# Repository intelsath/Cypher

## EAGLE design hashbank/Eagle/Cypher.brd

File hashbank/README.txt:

For database (SQLITE) use:
move sqlite3 to /usr/local/bin

For nodejs use:
move nodejs to /usr/bin

bin files in hashbank/bin

Update nodejs to latest version:
curl -sL https://deb.nodesource.com/setup_8.x | sudo -E bash -
sudo apt-get install -y nodejs

NFC
Follow the instructions at: https://www.nxp.com/docs/en/application-note/AN11697.pdf

move /NFC/conf/ files to /usr/local/etc
move /NFC/libs/ files to /usr/local/lib

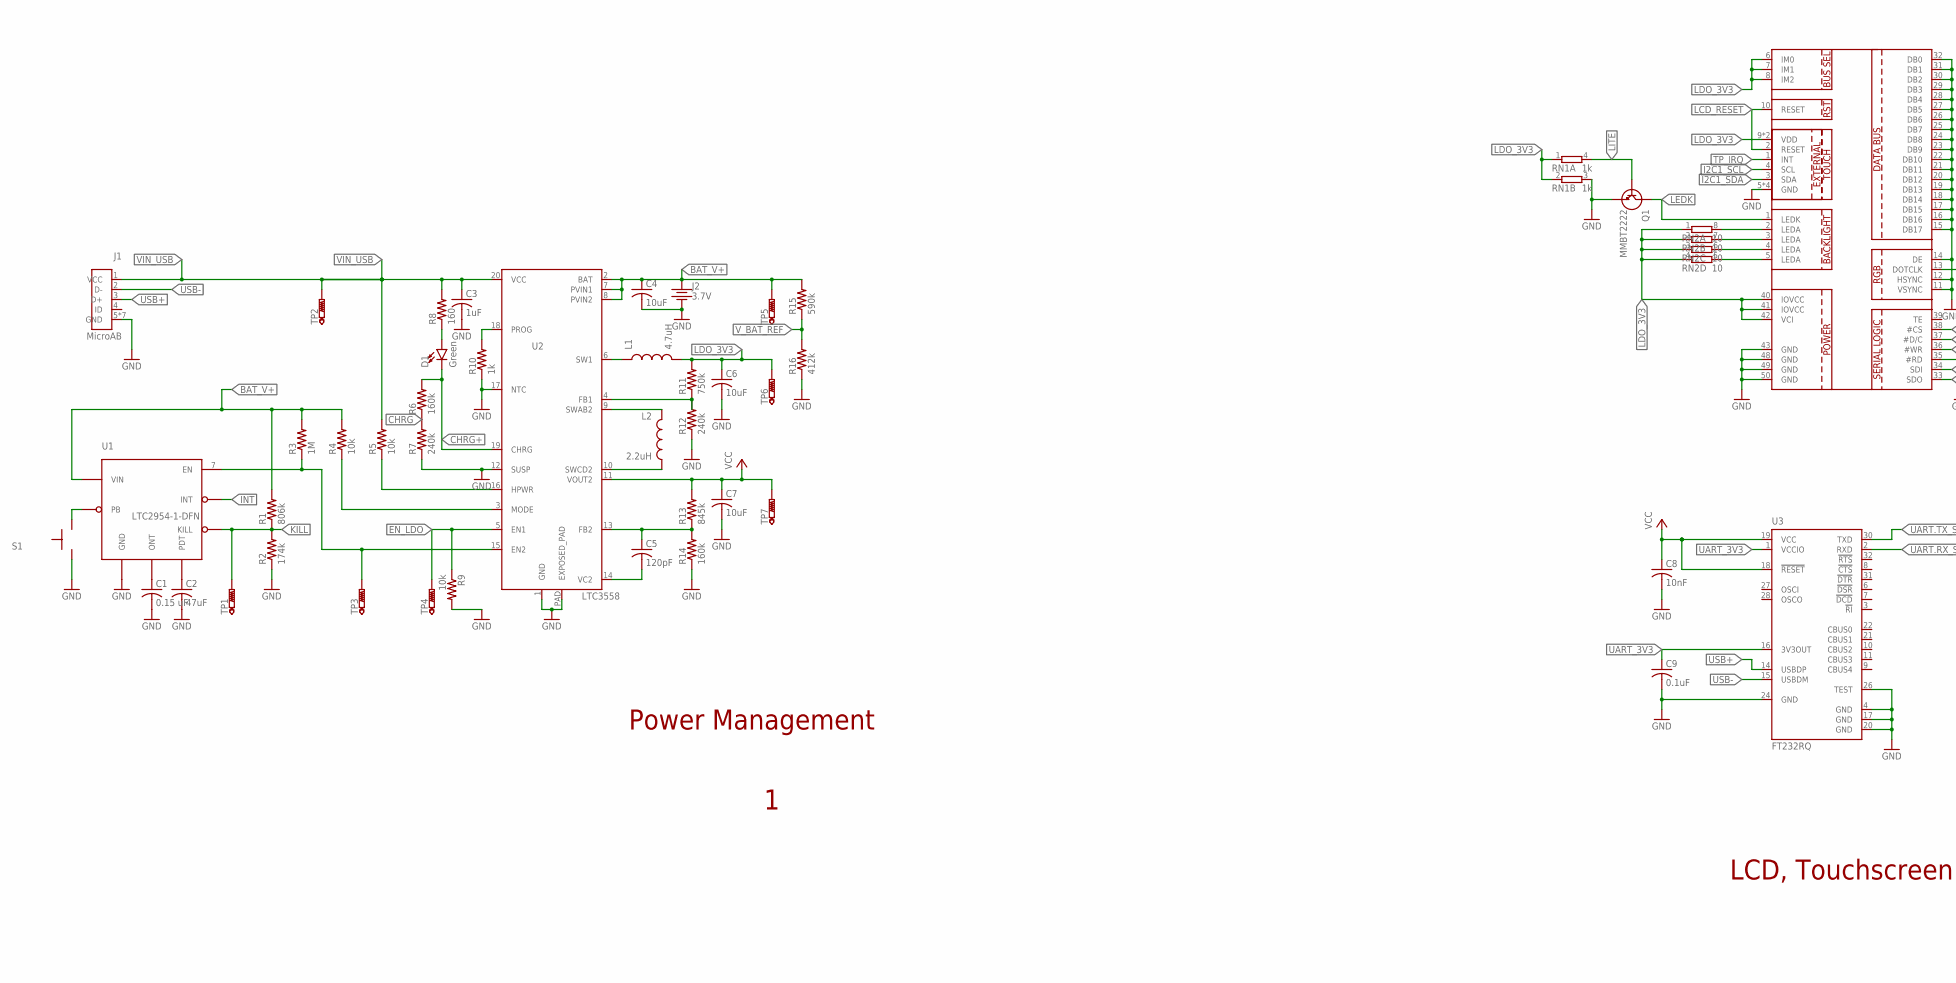
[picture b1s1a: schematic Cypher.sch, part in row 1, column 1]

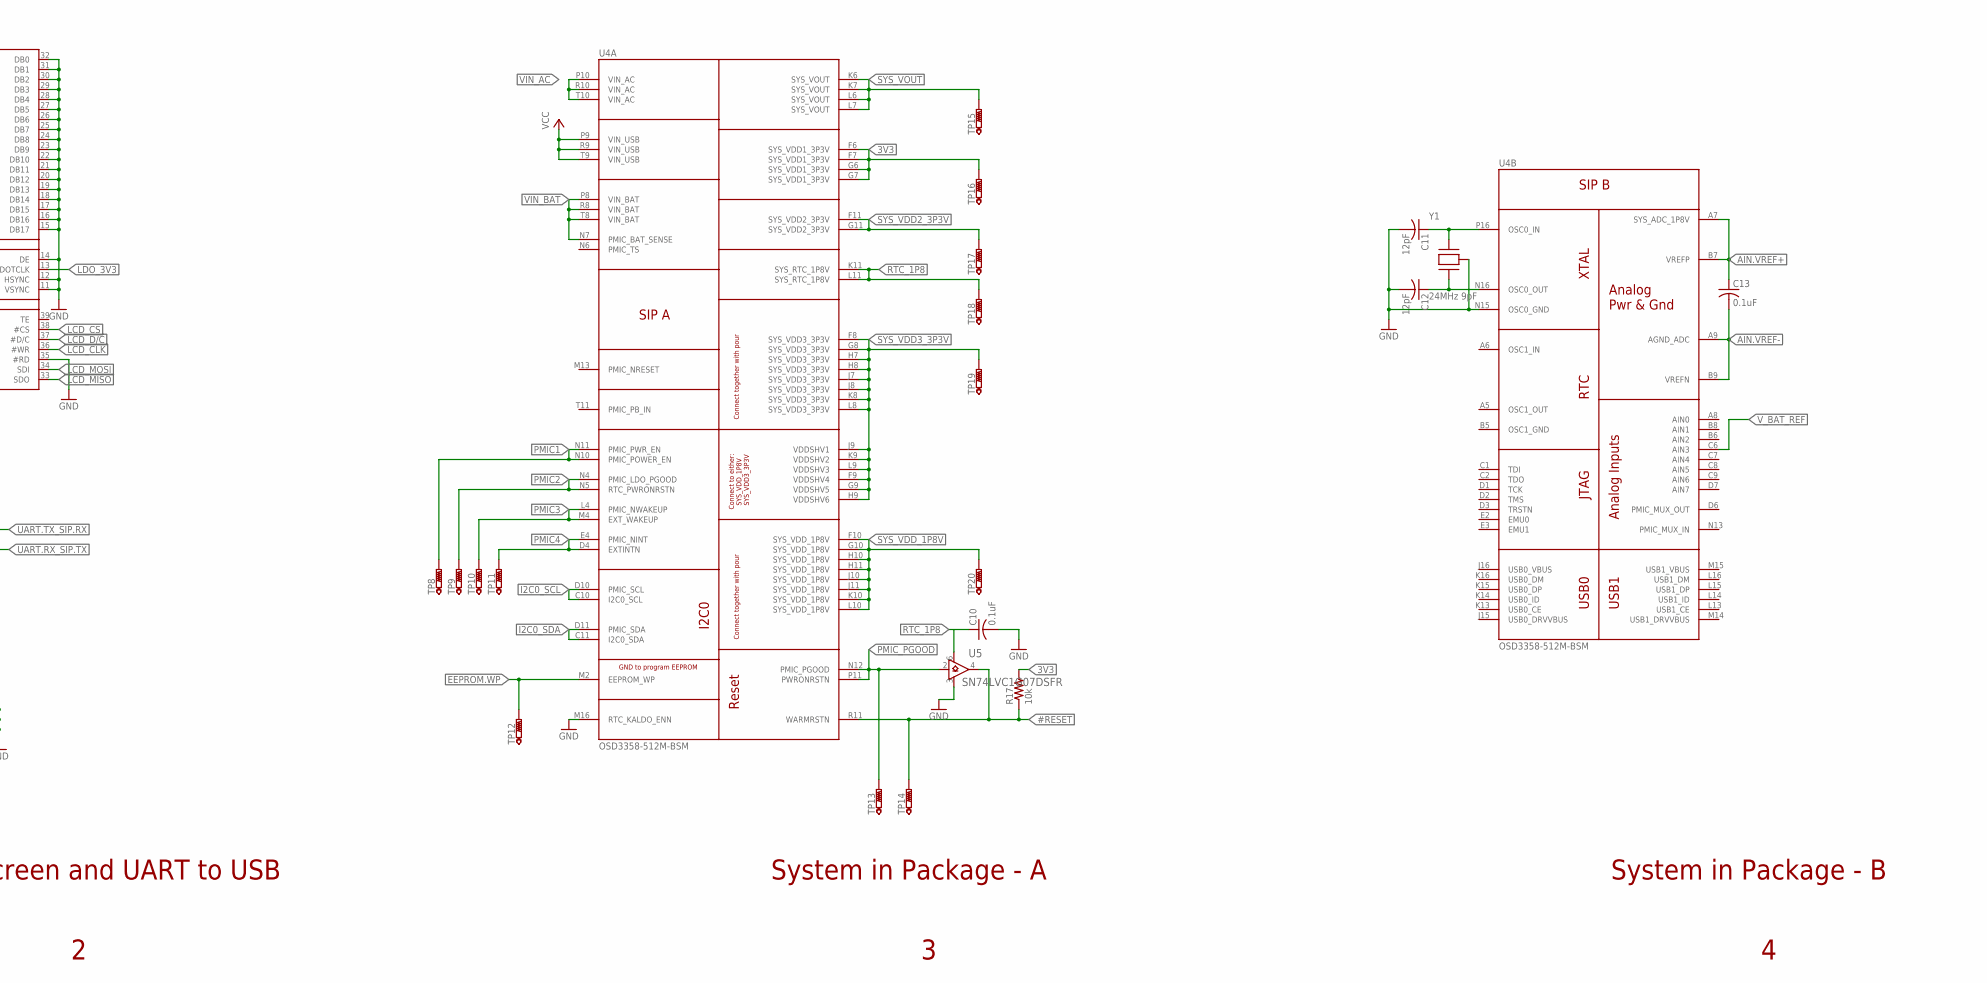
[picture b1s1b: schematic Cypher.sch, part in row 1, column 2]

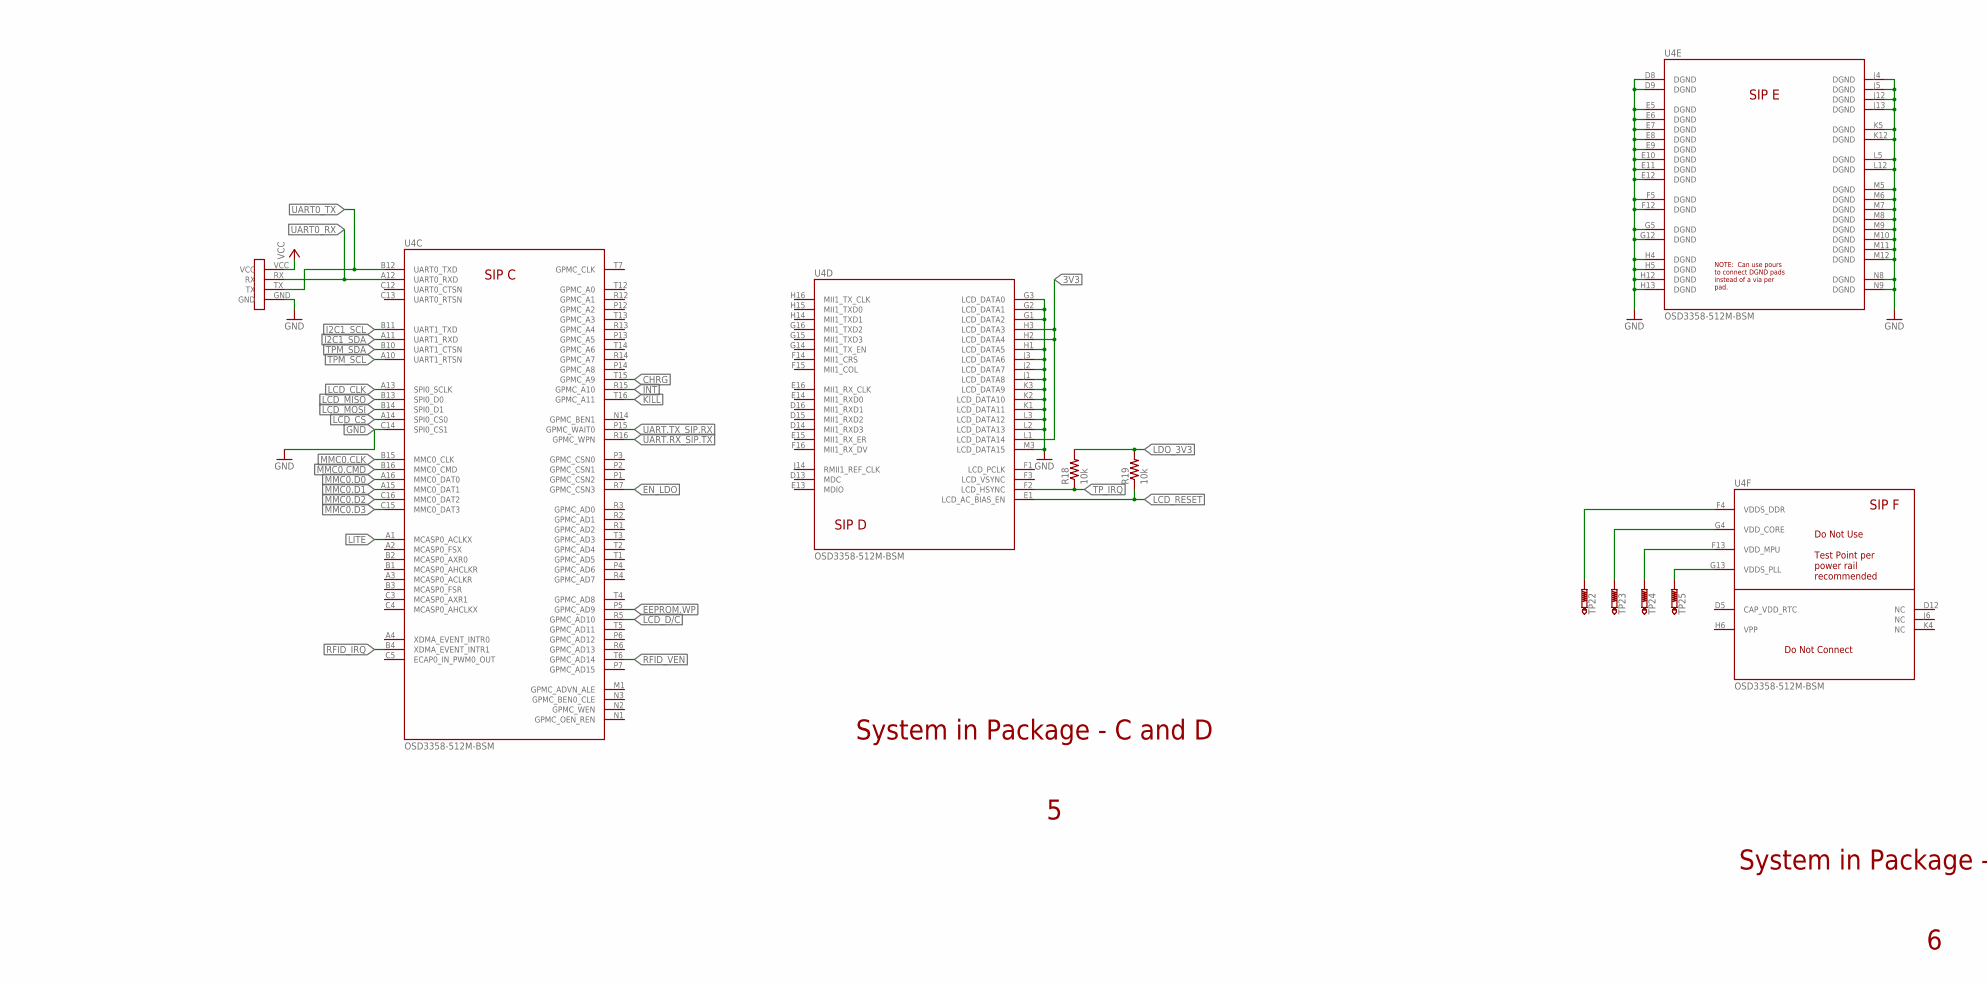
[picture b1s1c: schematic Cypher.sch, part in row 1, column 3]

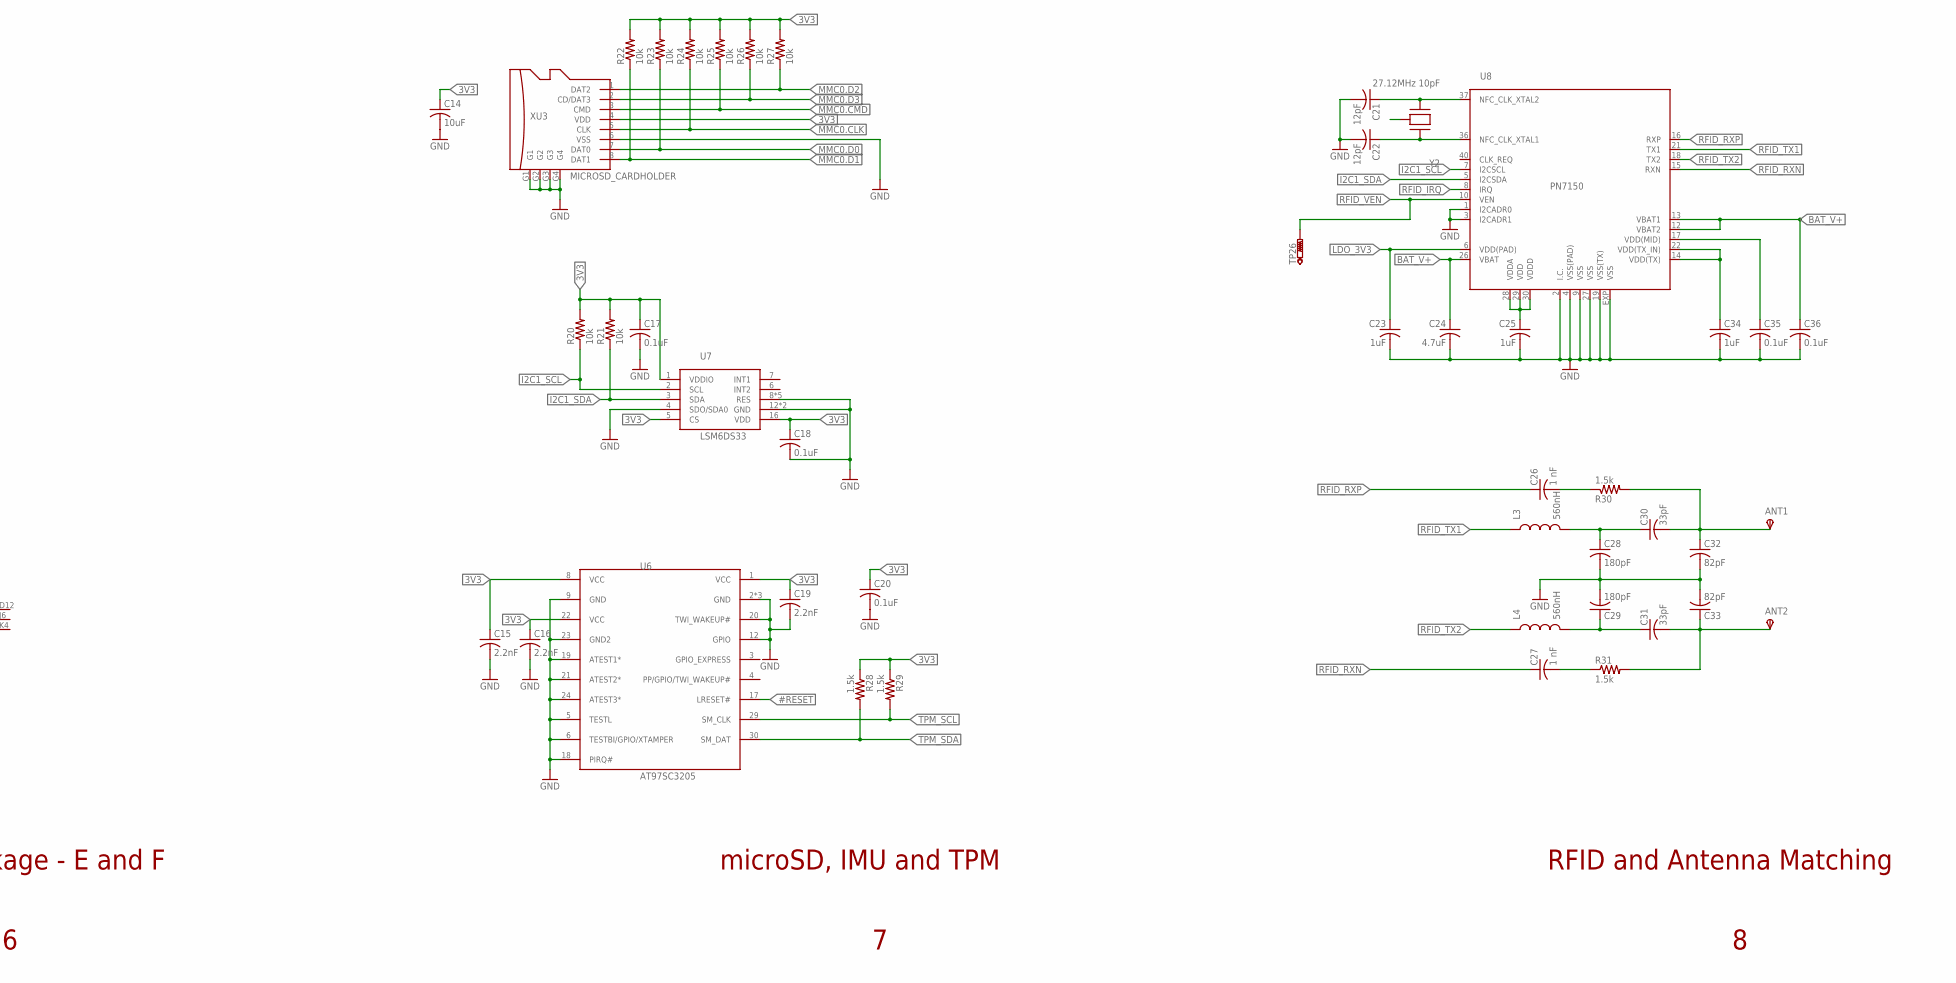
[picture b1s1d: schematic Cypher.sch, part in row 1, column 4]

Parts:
ANT1, ANT2: TPSB2,54; B2,54
C1: 0.15 uF; C0402
C2: 47uF; C0805
C3, C23, C25, C34: 1uF; C0201
C4, C6, C7, C14: 10uF; C0402
C5: 120pF; C0201
C8: 10nF; C0201
C9, C10, C13, C17, C18, C20, C35, C36: 0.1uF; C0201
C11, C12, C21, C22: 12pF; C0201
C15, C16, C19: 2.2nF; C0201
C24: 4.7uF; C0603
C26, C27: 1 nF; C0603
C28, C29: 180pF; C0201
C30, C31: 33pF; C0201
C32, C33: 82pF; C0201
D1: Green; LED-0603
J1: MicroAB; MICRO-USB-AB-SMD
J2: 3.7V; SH_CONNECTOR
L1: 4.7uH; L2520
L2: 2.2uH; L2520
L3, L4: 560nH; C0402
Q1: MMBT2222; 3-XFDFN
R1: 806k; R0201
R2: 174k; R0201
R3: 1M; R0201
R4, R5, R9, R17, R18, R19, R20, R21, R22, R23, R24, R25, R26, R27: 10k; R0201
R6, R14: 160k; R0201
R7, R12: 240k; R0201
R8: 160; R0402
R10: 1k; R0201
R11: 750k; R0201
R13: 845k; R0201
R15: 590k; R0201
R16: 412k; R0201
R28, R29: 1.5k; R0201
R30, R31: 1.5k; R0402
RN1: 1k; EXBV4V
RN2: 10; EXBN8V
S1: EVQ-P7JO1P; EVQ-P7J01P
TP1, TP2, TP3, TP4, TP5, TP6, TP7, TP8, TP9, TP10, TP11, TP12, TP13, TP14, TP15, TP16, TP17, TP18, TP19, TP20, TP22, TP23, TP24, TP25, TP26: PTR1B1,27; B1,27
TP21: UARTPINS
U1: LTC2954-1-DFN; DFN8-3MMX2MM
U2: LTC3558; QFN20-3MM
U3: FT232RQ; QFN32; MPN FT232RQ-REEL
U4: OSD3358-512M-BSM; OSD335X-BGA-256; MPN BB-POCKET
U5: SN74LVC1G07DSFR; SON35P100X100X40-6N
U6: AT97SC3205; QFN32-4MM
U7: LSM6DS33; LGA-16; MPN LSM6DS33TR
U8: PN7150; HVQFN40
XU1: CAPTOUCHSCREEN_6PINFPC10PIN; DF37B-10DM-0.4V
XU2: ILI9388_50PIN_SOCKET; FPC/FFC_50PIN_0.5MMPITCH
XU3: MICROSD_CARDHOLDER; HINGED_LID_MICROSD
Y1: 24MHz 9pF; 4-SMD
Y2: 27.12MHz 10pF; XRCGB

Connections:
3V3: C14.1, C15.1, C16.1, C17.1, C18.1, C19.1, C20.1, R17.2, R20.2, R21.2, R22.2, R23.2, R24.2, R25.2, R26.2, R27.2, R28.1, R29.1, TP16.TP, U4.F6 (SYS_VDD1_3P3V), U4.F7 (SYS_VDD1_3P3V), U4.G6 (SYS_VDD1_3P3V), U4.G7 (SYS_VDD1_3P3V), U4.H2 (LCD_DATA4), U4.H3 (LCD_DATA3), U4.L1 (LCD_DATA14), U6.1 (VCC), U6.8 (VCC), U6.22 (VCC), U7.1 (VDDIO), U7.5 (CS), U7.16 (VDD), XU3.4 (VDD)
#RESET: R17.1, TP14.TP, U4.R11 (WARMRSTN), U5.4 (Y), U6.17 (LRESET#)
AIN.VREF+: C13.1, U4.A7 (SYS_ADC_1P8V), U4.B7 (VREFP)
AIN.VREF-: C13.2, U4.A9 (AGND_ADC), U4.B9 (VREFN)
ANT_1: ANT1.TP, C30.2, C32.1, R30.2
ANT_2: ANT2.TP, C31.2, C33.1, R31.2
BAT_V+: C4.1, C24.1, C36.1, J2.1 (V+), R1.2, R3.2, R4.2, R15.2, TP5.TP, U1.4 (VIN), U2.2 (BAT), U2.7 (PVIN1), U2.8 (PVIN2), U8.12 (VBAT2), U8.13 (VBAT1), U8.26 (VBAT)
CHRG: R6.1, R7.2, U4.T15 (GPMC_A9)
CHRG+: D1.C, R6.2, U2.19 (CHRG)
EEPROM.WP: TP12.TP, U4.M2 (EEPROM_WP), U4.P5 (GPMC_AD9)
EMCF_ANTM1: C28.1, C30.1, L3.2
EMCF_ANTM2: C29.1, C31.1, L4.2
EN: R3.1, TP3.TP, U1.7 (EN), U2.15 (EN2)
EN_LDO: R9.1, TP4.TP, U2.5 (EN1), U4.R7 (GPMC_CSN3)
FB1: R11.1, R12.2, U2.4 (FB1)
FB2: C5.1, R13.1, R14.2, U2.13 (FB2)
GND: C1.2, C2.2, C3.2, C4.2, C6.2, C7.2, C8.2, C9.2, C10.2, C11.2, C12.2, C14.2, C15.2, C16.2, C17.2, C18.2, C19.2, C20.2, C21.2, C22.2, C23.2, C24.2, C25.2, C28.2, C29.2, C32.2, C33.2, C34.2, C35.2, C36.2, J1.5 (GND), J1.PAD1 (GND), J1.PAD2 (GND), J1.PAD3 (GND), J1.PAD4 (GND), J1.PAD5 (GND), J1.PAD6 (GND), J2.2 (V-), Q1.2 (E), R2.1, R7.1, R9.2, R10.1, R12.1, R14.1, R16.1, RN1.3 (2), S1.2, S1.2' (2), TP21.GND, U1.1 (GND), U1.EXP (GND), U2.1 (GND), U2.12 (SUSP), U2.17 (NTC), U2.PAD (EXPOSED_PAD), U3.4 (GND), U3.17 (GND), U3.20 (GND), U3.24 (GND), U3.26 (TEST), U4.C14 (SPI0_CS1), U4.D8 (DGND), U4.D9 (DGND), U4.E5 (DGND), U4.E6 (DGND), U4.E7 (DGND), U4.E8 (DGND), U4.E9 (DGND), U4.E10 (DGND), U4.E11 (DGND), U4.E12 (DGND), U4.F5 (DGND), U4.F12 (DGND), U4.G1 (LCD_DATA2), U4.G2 (LCD_DATA1), U4.G3 (LCD_DATA0), U4.G5 (DGND), U4.G12 (DGND), U4.H1 (LCD_DATA5), U4.H4 (DGND), U4.H5 (DGND), U4.H12 (DGND), U4.H13 (DGND), U4.J1 (LCD_DATA8), U4.J2 (LCD_DATA7), U4.J3 (LCD_DATA6), U4.J4 (DGND), U4.J5 (DGND), U4.J12 (DGND), U4.J13 (DGND), U4.K1 (LCD_DATA11), U4.K2 (LCD_DATA10), U4.K3 (LCD_DATA9), U4.K5 (DGND), U4.K12 (DGND), U4.L2 (LCD_DATA13), U4.L3 (LCD_DATA12), U4.L5 (DGND), U4.L12 (DGND), U4.M3 (LCD_DATA15), U4.M5 (DGND), U4.M6 (DGND), U4.M7 (DGND), U4.M8 (DGND), U4.M9 (DGND), U4.M10 (DGND), U4.M11 (DGND), U4.M12 (DGND), U4.M16 (RTC_KALDO_ENN), U4.N8 (DGND), U4.N9 (DGND), U4.N15 (OSC0_GND), U5.3 (GND), U6.2 (GND), U6.5 (TESTL), U6.6 (TESTBI/GPIO/XTAMPER), U6.9 (GND), U6.12 (GPIO), U6.18 (PIRQ#), U6.19 (ATEST1*), U6.20 (TWI_WAKEUP#), U6.21 (ATEST2*), U6.23 (GND2), U6.24 (ATEST3*), U6.32 (GND), U6.EXP (GND), U7.4 (SDO/SDA0), U7.8 (RES), U7.9 (RES), U7.10 (RES), U7.11 (RES), U7.12 (GND), U7.13 (GND), U7.15 (RES), U8.1 (I2CADR0), U8.2 (I.C.), U8.3 (I2CADR1), U8.4 (VSS(PAD)), U8.9 (VSS), U8.19 (VSS(TX)), U8.27 (VSS), U8.EXP (VSS), XU1.5 (GND), XU1.6 (GND), XU1.7 (GND), XU1.8 (GND), XU2.11 (VSYNC), XU2.12 (HSYNC), XU2.14 (DE), XU2.15 (DB17), XU2.16 (DB16), XU2.17 (DB15), XU2.18 (DB14), XU2.19 (DB13), XU2.20 (DB12), XU2.21 (DB11), XU2.22 (DB10), XU2.23 (DB9), XU2.24 (DB8), XU2.25 (DB7), XU2.26 (DB6), XU2.27 (DB5), XU2.28 (DB4), XU2.29 (DB3), XU2.30 (DB2), XU2.31 (DB1), XU2.32 (DB0), XU2.35 (#RD), XU2.43 (GND), XU2.48 (GND), XU2.49 (GND), XU2.50 (GND), XU3.6 (VSS), XU3.G1, XU3.G2, XU3.G3, XU3.G4, Y1.2 (GND), Y1.4 (GND)
HPWR: R5.1, U2.16 (HPWR)
I2C0_SCL: U4.C10 (I2C0_SCL), U4.D10 (PMIC_SCL)
I2C0_SDA: U4.C11 (I2C0_SDA), U4.D11 (PMIC_SDA)
I2C1_SCL: R20.1, U4.B11 (UART1_TXD), U7.2 (SCL), U8.7 (I2CSCL), XU1.4 (SCL)
I2C1_SDA: R21.1, U4.A11 (UART1_RXD), U7.3 (SDA), U8.5 (I2CSDA), XU1.3 (SDA)
INT: U1.8 (INT), U4.R15 (GPMC_A10)
KILL: R1.1, R2.2, TP1.TP, U1.5 (KILL), U4.T16 (GPMC_A11)
LCD_CLK: U4.A13 (SPI0_SCLK), XU2.36 (#WR)
LCD_CS: U4.A14 (SPI0_CS0), XU2.38 (#CS)
LCD_D/C: U4.R5 (GPMC_AD10), XU2.37 (#D/C)
LCD_MISO: U4.B13 (SPI0_D0), XU2.33 (SDO)
LCD_MOSI: U4.B14 (SPI0_D1), XU2.34 (SDI)
LCD_RESET: R19.1, U4.E1 (LCD_AC_BIAS_EN), XU1.2 (RESET), XU2.10 (RESET)
LDO_3V3: C6.1, C23.1, L1.2, R11.2, R18.2, R19.2, RN1.1, RN1.2 (1), RN2.1, RN2.2 (1), RN2.3 (1), RN2.4 (1), TP6.TP, U8.6 (VDD(PAD)), XU1.9 (VDD), XU1.10 (VDD), XU2.6 (IM0), XU2.7 (IM1), XU2.8 (IM2), XU2.13 (DOTCLK), XU2.40 (IOVCC), XU2.41 (IOVCC), XU2.42 (VCI)
LDO_BOOSTER_MODE: R4.1, U2.3 (MODE)
LEDA@2: RN2.8 (2), XU2.2 (LEDA)
LEDA@3: RN2.7 (2), XU2.3 (LEDA)
LEDA@4: RN2.6 (2), XU2.4 (LEDA)
LEDA@5: RN2.5 (2), XU2.5 (LEDA)
LEDK: Q1.3 (C), XU2.1 (LEDK)
LED_A: D1.A, R8.1
LITE: Q1.1 (B), RN1.4 (2), U4.A1 (MCASP0_ACLKX)
MMC0.CLK: R24.1, U4.B15 (MMC0_CLK), XU3.5 (CLK)
MMC0.CMD: R25.1, U4.B16 (MMC0_CMD), XU3.3 (CMD)
MMC0.D0: R23.1, U4.A16 (MMC0_DAT0), XU3.7 (DAT0)
MMC0.D1: R22.1, U4.A15 (MMC0_DAT1), XU3.8 (DAT1)
MMC0.D2: R27.1, U4.C16 (MMC0_DAT2), XU3.1 (DAT2)
MMC0.D3: R26.1, U4.C15 (MMC0_DAT3), XU3.2 (CD/DAT3)
NC: Y2.2 (GND), Y2.4 (GND)
ON_T: C1.1, U1.2 (ONT)
PB: S1.1, S1.1' (1), U1.3 (PB)
PD_T: C2.1, U1.6 (PDT)
PMIC1: TP8.TP, U4.N10 (PMIC_POWER_EN), U4.N11 (PMIC_PWR_EN)
PMIC2: TP9.TP, U4.N4 (PMIC_LDO_PGOOD), U4.N5 (RTC_PWRONRSTN)
PMIC3: TP10.TP, U4.L4 (PMIC_NWAKEUP), U4.M4 (EXT_WAKEUP)
PMIC4: TP11.TP, U4.D4 (EXTINTN), U4.E4 (PMIC_NINT)
PMIC_PGOOD: TP13.TP, U4.N12 (PMIC_PGOOD), U4.P11 (PWRONRSTN), U5.2 (A)
PROG: R10.2, U2.18 (PROG)
RFID_IRQ: U4.B4 (XDMA_EVENT_INTR1), U8.8 (IRQ)
RFID_MISC_1: C26.2, R30.1
RFID_MISC_2: C27.2, R31.1
RFID_OSC_IN: C22.1, U8.36 (NFC_CLK_XTAL1), Y2.1 (OSC_IN)
RFID_OSC_OUT: C21.1, U8.37 (NFC_CLK_XTAL2), Y2.3 (OSC_OUT)
RFID_RXN: C27.1, U8.15 (RXN)
RFID_RXP: C26.1, U8.16 (RXP)
RFID_TX1: L3.1, U8.21 (TX1)
RFID_TX2: L4.1, U8.18 (TX2)
RFID_VEN: TP26.TP, U4.T6 (GPMC_AD14), U8.10 (VEN)
RTC_1P8: C10.1, TP18.TP, U4.K11 (SYS_RTC_1P8V), U4.L11 (SYS_RTC_1P8V), U5.6 (VCC)
SIP_OSC_IN: C11.1, U4.P16 (OSC0_IN), Y1.1 (OSC_IN)
SIP_OSC_OUT: C12.1, U4.N16 (OSC0_OUT), Y1.3 (OSC_OUT)
SW1: L1.1, U2.6 (SW1)
SWAB2: L2.1, U2.9 (SWAB2)
SWCD2: L2.2, U2.10 (SWCD2)
SYS_VDD2_3P3V: TP17.TP, U4.F11 (SYS_VDD2_3P3V), U4.G11 (SYS_VDD2_3P3V)
SYS_VDD3_3P3V: TP19.TP, U4.F8 (SYS_VDD3_3P3V), U4.F9 (VDDSHV4), U4.G8 (SYS_VDD3_3P3V), U4.G9 (VDDSHV5), U4.H7 (SYS_VDD3_3P3V), U4.H8 (SYS_VDD3_3P3V), U4.H9 (VDDSHV6), U4.J7 (SYS_VDD3_3P3V), U4.J8 (SYS_VDD3_3P3V), U4.J9 (VDDSHV1), U4.K8 (SYS_VDD3_3P3V), U4.K9 (VDDSHV2), U4.L8 (SYS_VDD3_3P3V), U4.L9 (VDDSHV3)
SYS_VDD_1P8V: TP20.TP, U4.F10 (SYS_VDD_1P8V), U4.G10 (SYS_VDD_1P8V), U4.H10 (SYS_VDD_1P8V), U4.H11 (SYS_VDD_1P8V), U4.J10 (SYS_VDD_1P8V), U4.J11 (SYS_VDD_1P8V), U4.K10 (SYS_VDD_1P8V), U4.L10 (SYS_VDD_1P8V)
SYS_VOUT: TP15.TP, U4.K6 (SYS_VOUT), U4.K7 (SYS_VOUT), U4.L6 (SYS_VOUT), U4.L7 (SYS_VOUT)
TPM_SCL: R29.2, U4.A10 (UART1_RTSN), U6.29 (SM_CLK)
TPM_SDA: R28.2, U4.B10 (UART1_CTSN), U6.30 (SM_DAT)
TP_IRQ: R18.1, U4.F2 (LCD_HSYNC), XU1.1 (INT)
UART0_RX: TP21.RX, U4.A12 (UART0_RXD)
UART0_TX: TP21.TX, U4.B12 (UART0_TXD)
UART.RX_SIP.TX: U3.2 (RXD), U4.R16 (GPMC_WPN)
UART.TX_SIP.RX: U3.30 (TXD), U4.P15 (GPMC_WAIT0)
UART_3V3: C9.1, U3.1 (VCCIO), U3.16 (3V3OUT)
USB+: J1.3 (D+), U3.14 (USBDP)
USB-: J1.2 (D-), U3.15 (USBDM)
VC2: C5.2, U2.14 (VC2)
VCC: C7.1, C8.1, R13.2, TP7.TP, TP21.VCC, U2.11 (VOUT2), U3.18 (!RESET), U3.19 (VCC), U4.P9 (VIN_USB), U4.R9 (VIN_USB), U4.T9 (VIN_USB)
VDD: C25.1, U8.28 (VDDA), U8.29 (VDD), U8.30 (VDDD)
VDD(MID): C35.1, U8.17 (VDD(MID))
VDD(TX): C34.1, U8.14 (VDD(TX)), U8.22 (VDD(TX_IN))
VDDS_DDR: TP22.TP, U4.F4 (VDDS_DDR)
VDDS_PLL: TP25.TP, U4.G13 (VDDS_PLL)
VDD_CORE: TP23.TP, U4.G4 (VDD_CORE)
VDD_MPU: TP24.TP, U4.F13 (VDD_MPU)
VIN_AC: U4.P10 (VIN_AC), U4.R10 (VIN_AC), U4.T10 (VIN_AC)
VIN_BAT: U4.N7 (PMIC_BAT_SENSE), U4.P8 (VIN_BAT), U4.R8 (VIN_BAT), U4.T8 (VIN_BAT)
VIN_USB: C3.1, J1.1 (VCC), R5.2, R8.2, TP2.TP, U2.20 (VCC)
V_BAT_REF: R15.1, R16.2, U4.C6 (AIN3)

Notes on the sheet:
Power Management
LCD, Touchscreen and UART to USB
System in Package - A
System in Package - B
System in Package - C and D
System in Package - E and F
microSD, IMU and TPM
RFID and Antenna Matching

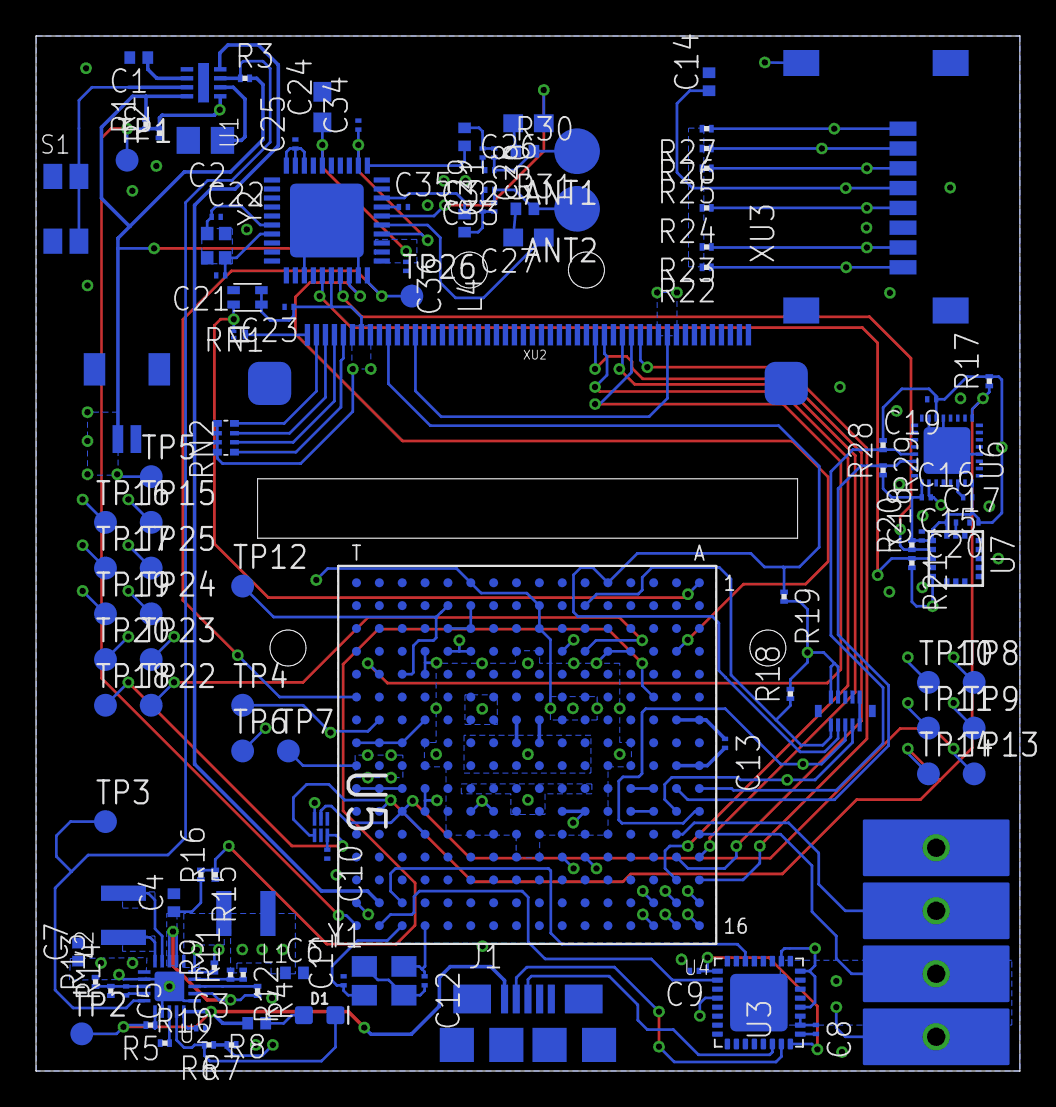
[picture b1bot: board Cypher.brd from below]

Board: 4 copper layers, 54.7 x 57.5 mm, 119 parts (119 on the bottom side), 98 nets.

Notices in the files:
Hardware/Eagle/Cypher - V0.4.brd:
© 2018 Megahash Corp
parts and their libraries:
SparkFun-LED: Licensing: Creative Commons ShareAlike 4.0 International - https://creativecommons.org/licenses/by-sa/4.0
